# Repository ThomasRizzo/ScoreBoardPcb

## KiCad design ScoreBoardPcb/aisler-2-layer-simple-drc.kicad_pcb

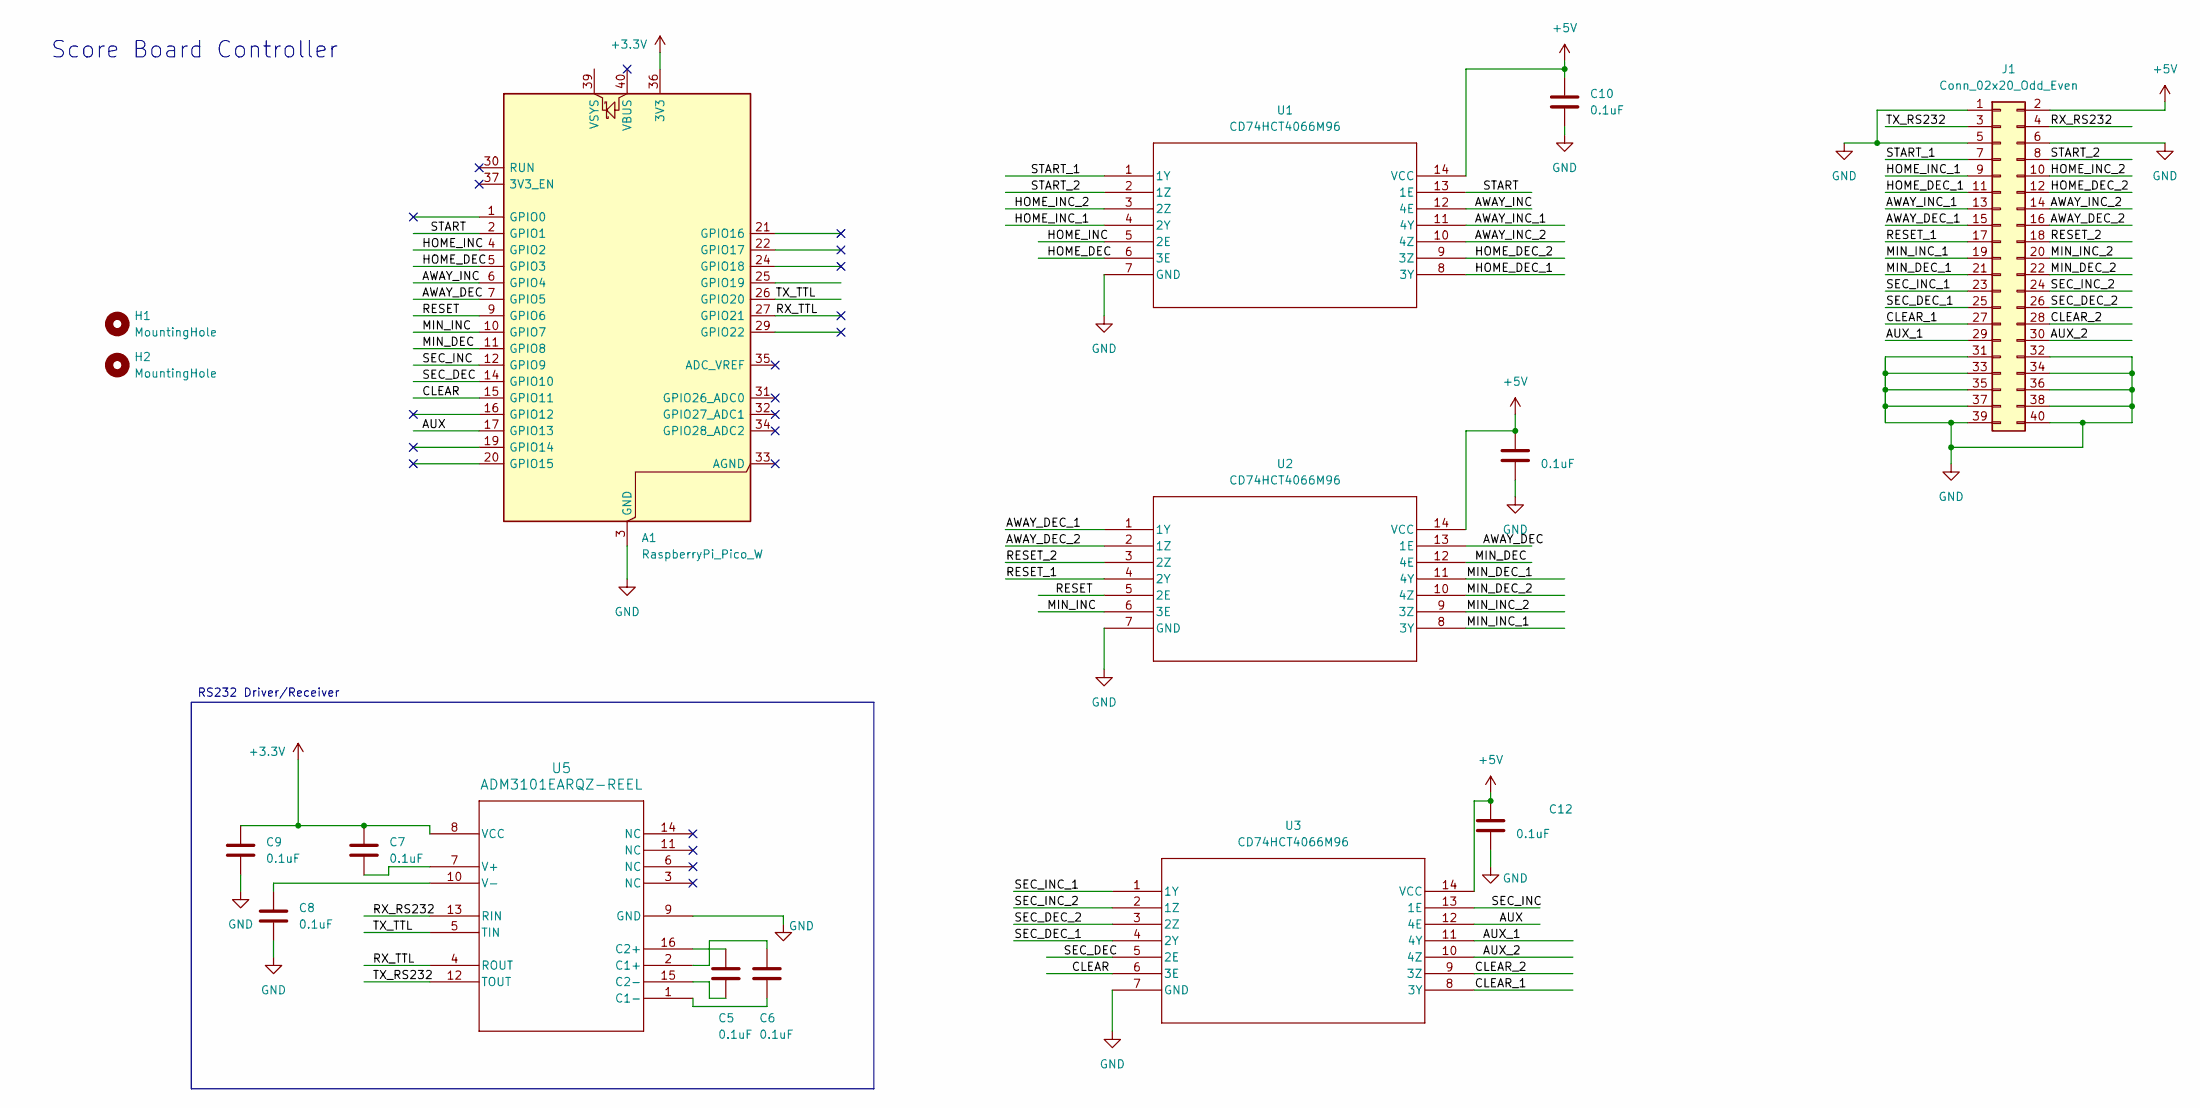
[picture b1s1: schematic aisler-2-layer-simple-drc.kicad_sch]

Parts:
A1: RaspberryPi_Pico_W; RaspberryPi_Pico_Common_THT
C5, C6, C7, C8, C9, C10, C12, C13: 0.1uF; C_0402_1005Metric_Pad0.74x0.62mm_HandSolder
H1, H2: MountingHole; MountingHole_3.2mm_M3
J1: Conn_02x20_Odd_Even; IDC-Header_2x20_P2.54mm_Vertical_SMD
U1, U2, U3: CD74HCT4066M96; D14-M; PARTREV G
U5: ADM3101EARQZ-REEL; RQ_16_ADI

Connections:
+3.3V: A1.36 (3V3), C7.1, C9.1, U5.8 (VCC)
+5V: C10.1, C12.1, C13.1, J1.2, U1.14 (VCC), U2.14 (VCC), U3.14 (VCC)
/AUX: A1.17 (GPIO13), U3.12 (4E)
/AUX_1: J1.29, U3.11 (4Y)
/AUX_2: J1.30, U3.10 (4Z)
/AWAY_DEC: A1.7 (GPIO5), U2.13 (1E)
/AWAY_DEC_1: J1.15, U2.1 (1Y)
/AWAY_DEC_2: J1.16, U2.2 (1Z)
/AWAY_INC: A1.6 (GPIO4), U1.12 (4E)
/AWAY_INC_1: J1.13, U1.11 (4Y)
/AWAY_INC_2: J1.14, U1.10 (4Z)
/CLEAR: A1.15 (GPIO11), U3.6 (3E)
/CLEAR_1: J1.27, U3.8 (3Y)
/CLEAR_2: J1.28, U3.9 (3Z)
/HOME_DEC: A1.5 (GPIO3), U1.6 (3E)
/HOME_DEC_1: J1.11, U1.8 (3Y)
/HOME_DEC_2: J1.12, U1.9 (3Z)
/HOME_INC: A1.4 (GPIO2), U1.5 (2E)
/HOME_INC_1: J1.9, U1.4 (2Y)
/HOME_INC_2: J1.10, U1.3 (2Z)
/MIN_DEC: A1.11 (GPIO8), U2.12 (4E)
/MIN_DEC_1: J1.21, U2.11 (4Y)
/MIN_DEC_2: J1.22, U2.10 (4Z)
/MIN_INC: A1.10 (GPIO7), U2.6 (3E)
/MIN_INC_1: J1.19, U2.8 (3Y)
/MIN_INC_2: J1.20, U2.9 (3Z)
/RESET: A1.9 (GPIO6), U2.5 (2E)
/RESET_1: J1.17, U2.4 (2Y)
/RESET_2: J1.18, U2.3 (2Z)
/RX_RS232: J1.4, U5.13 (RIN)
/RX_TTL: A1.27 (GPIO21), U5.4 (ROUT)
/SEC_DEC: A1.14 (GPIO10), U3.5 (2E)
/SEC_DEC_1: J1.25, U3.4 (2Y)
/SEC_DEC_2: J1.26, U3.3 (2Z)
/SEC_INC: A1.12 (GPIO9), U3.13 (1E)
/SEC_INC_1: J1.23, U3.1 (1Y)
/SEC_INC_2: J1.24, U3.2 (1Z)
/START: A1.2 (GPIO1), U1.13 (1E)
/START_1: J1.7, U1.1 (1Y)
/START_2: J1.8, U1.2 (1Z)
/TX_RS232: J1.3, U5.12 (TOUT)
/TX_TTL: A1.26 (GPIO20), U5.5 (TIN)
GND: A1.3 (GND), A1.8 (GND), A1.13 (GND), A1.18 (GND), A1.23 (GND), A1.28 (GND), A1.38 (GND), C8.2, C9.2, C10.2, C12.2, C13.2, J1.1, J1.5, J1.6, J1.31, J1.32, J1.33, J1.34, J1.35, J1.36, J1.37, J1.38, J1.39, J1.40, U1.7 (GND), U2.7 (GND), U3.7 (GND), U5.9 (GND)
unnamed: C6.1, U5.2 (C1+)
unnamed: C6.2, U5.1 (C1-)
unnamed: C5.1, U5.16 (C2+)
unnamed: C5.2, U5.15 (C2-)
unnamed: C7.2, U5.7 (V+)
unnamed: C8.1, U5.10 (V-)

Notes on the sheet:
RS232 Driver/Receiver
Score Board Controller

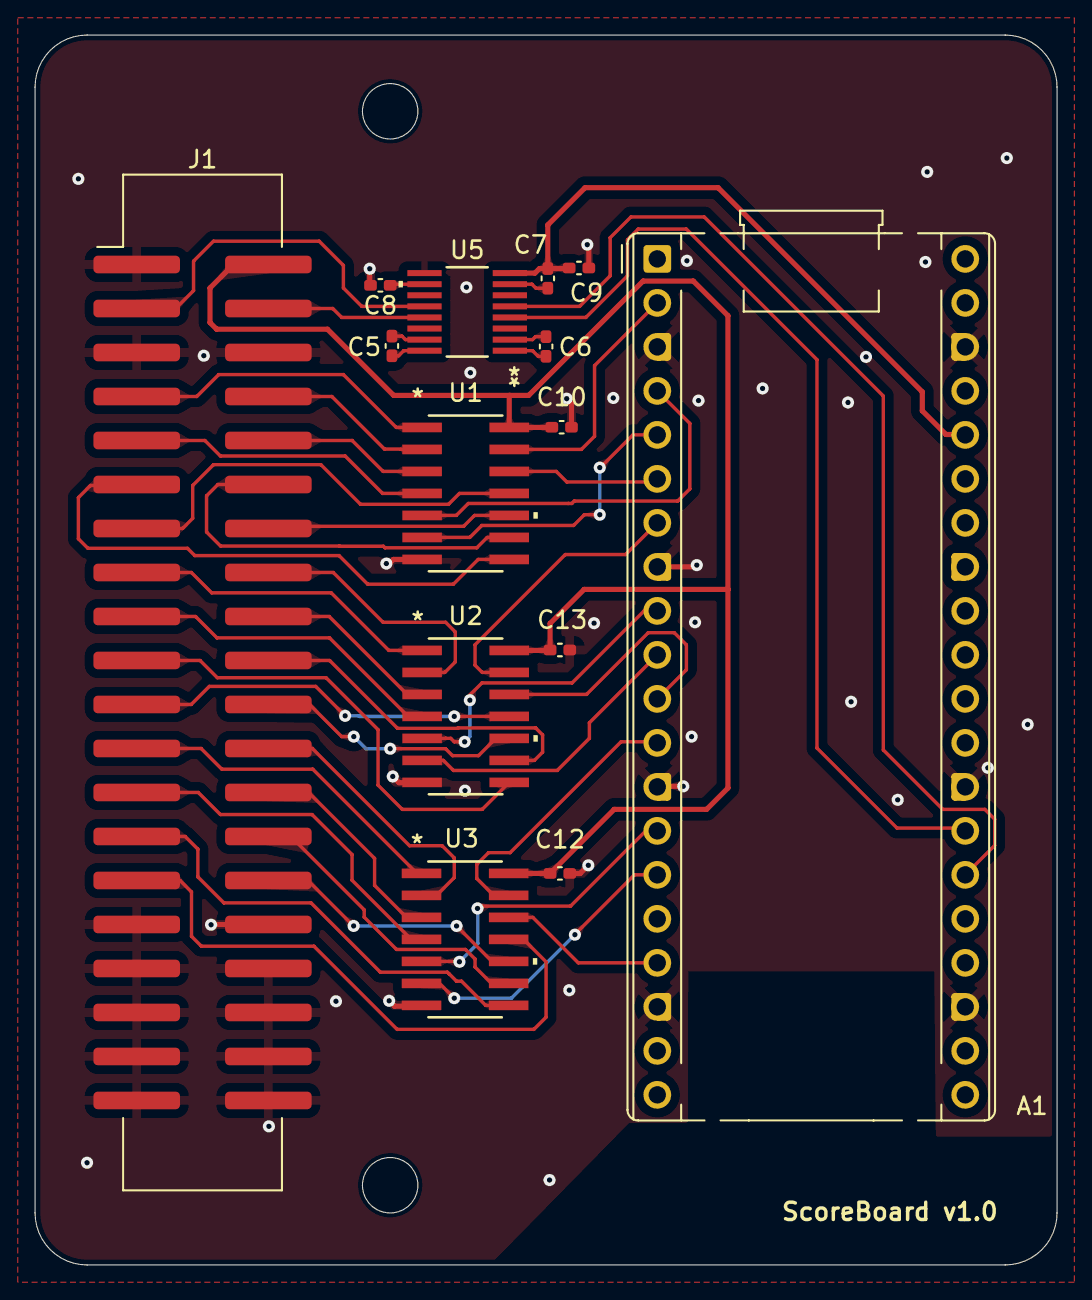
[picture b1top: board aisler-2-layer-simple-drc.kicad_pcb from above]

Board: 2 copper layers, 59.0 x 71.0 mm, 16 parts (0 on the bottom side), 49 nets.

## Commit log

2025-05-17 Initial
2025-05-17 Routed with mounting holes
2025-05-17 Add README.md
2025-05-17 Update to use CD74HCT4066M96
2025-05-21 Rev 1.0 submitted for manf
2025-05-21 Update image
